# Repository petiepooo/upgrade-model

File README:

Programs: 
LED_DMA.py                 python program to run various LED patterns, including data -h gives the options
LED_DMA.c                  barebone c program that is called by LED_DMA.py to fill direct memory buffer
LED_DMA                    test shell script to run LED_DMA.py (setting all LEDs to red)
SLIDE_SHOW                 shell program to run various patterns and data displays
rpi                        directory that hosts utility program for DMA SMI access
data                       directory that holds json files with simulated data 
compile_LED_DMA            shell script to make shared library from test_LED_DMA.c
gitcommit                  program to run git from rpi to update master repository (note that you have to include an "add" for new programs )

older programs: 
test_string                shell script to run standard Python interface on GPIO18 with hardware PWA
compile_test_ctypes        shell script to make shared library from test_ctypes.c
test_ctypes.c              c program connected to test_ctypes.py
test_ctypes.py             python script to test c program access via ctypes 
test_ctypes                shell script to run test_ctypes.py with python3

The hdmi connection to the screen disturbes the precision of the hardware output to steer the LEDs. Therefore, the video needs to be turned off: 
In fact, the recommended method to run the rpi headless and start the program via tcp from a remote computer

https://www.elektronik-kompendium.de/sites/raspberry-pi/2111101.htm
/opt/vc/bin/tvservice -p; sudo /bin/chvt 6; sudo /bin/chvt 7 (gui)
/opt/vc/bin/tvservice -p; sudo /bin/chvt 2; sudo /bin/chvt 1 (console)

There also a set of software to run  o n e  LED strip using the PWR hardware clock. Here are the instruction to set up this code. You can use test_string to run a test program. 

https://tutorials-raspberrypi.de/raspberry-pi-ws2812-ws2811b-rgb-led-streifen-steuern/
provides instructions on how to install the rpi_ws281x software:

sudo apt-get update
sudo apt-get install gcc make build-essential python-dev git scons swig
sudo nano /etc/modprobe.d/snd-blacklist.conf   enter: blacklist snd_bcm2835    (in order to disable audio)
sudo nano /boot/config.txt : # Enable audio (loads snd_bcm2835)  #dtparam=audio=on (comment out)
sudo reboot
git clone https://github.com/jgarff/rpi_ws281x
cd rpi_ws281x/  : sudo scons     compile everything
sudo python3 setup.py build
sudo python3 setup.py install
sudo pip3 install adafruit-circuitpython-neopixel

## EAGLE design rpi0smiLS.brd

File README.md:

# Upgrade Model

This git repository collects programs to run a 1000+ LED model of IceCube DeepCore + Phase 1

Cloned into github from https://gitlab.rlp.net/koepke/upgrade-model

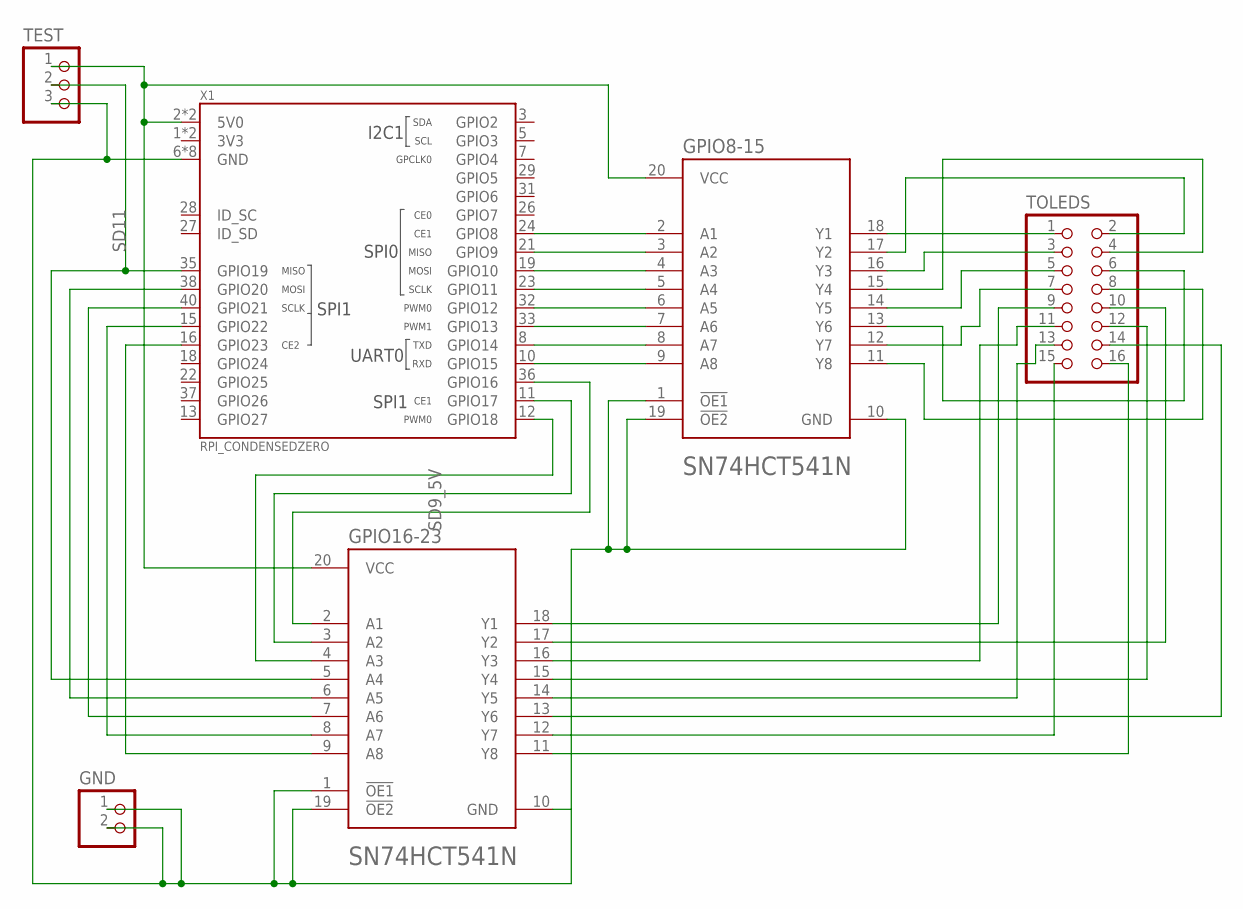
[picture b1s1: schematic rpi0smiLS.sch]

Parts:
GND: PINHD-1X2; 1X02
GPIO8-15, GPIO16-23: TEXAS_INSTRUMENTS_SN74HCT541NTEXAS_INSTRUMENTS_SN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; TEXAS_INSTRUMENTS_SN74HCT541N_0
TEST: PINHD-1X3; 1X03
TOLEDS: PINHD-2X8; 2X08
X1: RPI_CONDENSEDZERO; RPI_ZERO_THT

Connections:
3V3: X1.1 (3V3), X1.17 (3V3)
GND: GND.1, GND.2, GPIO8-15.1 (!OE1!), GPIO8-15.10 (GND), GPIO8-15.19 (!OE2!), GPIO16-23.1 (!OE1!), GPIO16-23.10 (GND), GPIO16-23.19 (!OE2!), TEST.3, X1.6 (GND), X1.9 (GND), X1.14 (GND), X1.20 (GND), X1.25 (GND), X1.30 (GND), X1.34 (GND), X1.39 (GND)
PWR: GPIO8-15.20 (VCC), GPIO16-23.20 (VCC), TEST.1, X1.2 (5V0), X1.4 (5V0)
SD0: GPIO8-15.2 (A1), X1.24 (GPIO8)
SD0_5V: GPIO8-15.18 (Y1), TOLEDS.1
SD1: GPIO8-15.3 (A2), X1.21 (GPIO9)
SD1_5V: GPIO8-15.17 (Y2), TOLEDS.2
SD2: GPIO8-15.4 (A3), X1.19 (GPIO10)
SD2_5V: GPIO8-15.16 (Y3), TOLEDS.3
SD3: GPIO8-15.5 (A4), X1.23 (GPIO11)
SD3_5V: GPIO8-15.15 (Y4), TOLEDS.4
SD4: GPIO8-15.6 (A5), X1.32 (GPIO12)
SD4_5V: GPIO8-15.14 (Y5), TOLEDS.5
SD5: GPIO8-15.7 (A6), X1.33 (GPIO13)
SD5_5V: GPIO8-15.13 (Y6), TOLEDS.6
SD6: GPIO8-15.8 (A7), X1.8 (GPIO14)
SD6_5V: GPIO8-15.12 (Y7), TOLEDS.7
SD7: GPIO8-15.9 (A8), X1.10 (GPIO15)
SD7_5V: GPIO8-15.11 (Y8), TOLEDS.8
SD8: GPIO16-23.2 (A1), X1.36 (GPIO16)
SD8_5V: GPIO16-23.18 (Y1), TOLEDS.9
SD9: GPIO16-23.3 (A2), X1.11 (GPIO17)
SD9_5V: GPIO16-23.17 (Y2), TOLEDS.10
SD10: GPIO16-23.4 (A3), X1.12 (GPIO18)
SD11: GPIO16-23.5 (A4), TEST.2, X1.35 (GPIO19)
SD11_5V: GPIO16-23.15 (Y4), TOLEDS.12
SD12: GPIO16-23.6 (A5), X1.38 (GPIO20)
SD12_5V: GPIO16-23.14 (Y5), TOLEDS.13
SD13: GPIO16-23.7 (A6), X1.40 (GPIO21)
SD13_5V: GPIO16-23.13 (Y6), TOLEDS.14
SD14: GPIO16-23.8 (A7), X1.15 (GPIO22)
SD14_5V: GPIO16-23.12 (Y7), TOLEDS.15
SD15: GPIO16-23.9 (A8), X1.16 (GPIO23)
SD15_5V: GPIO16-23.11 (Y8), TOLEDS.16
SD_10_5V: GPIO16-23.16 (Y3), TOLEDS.11

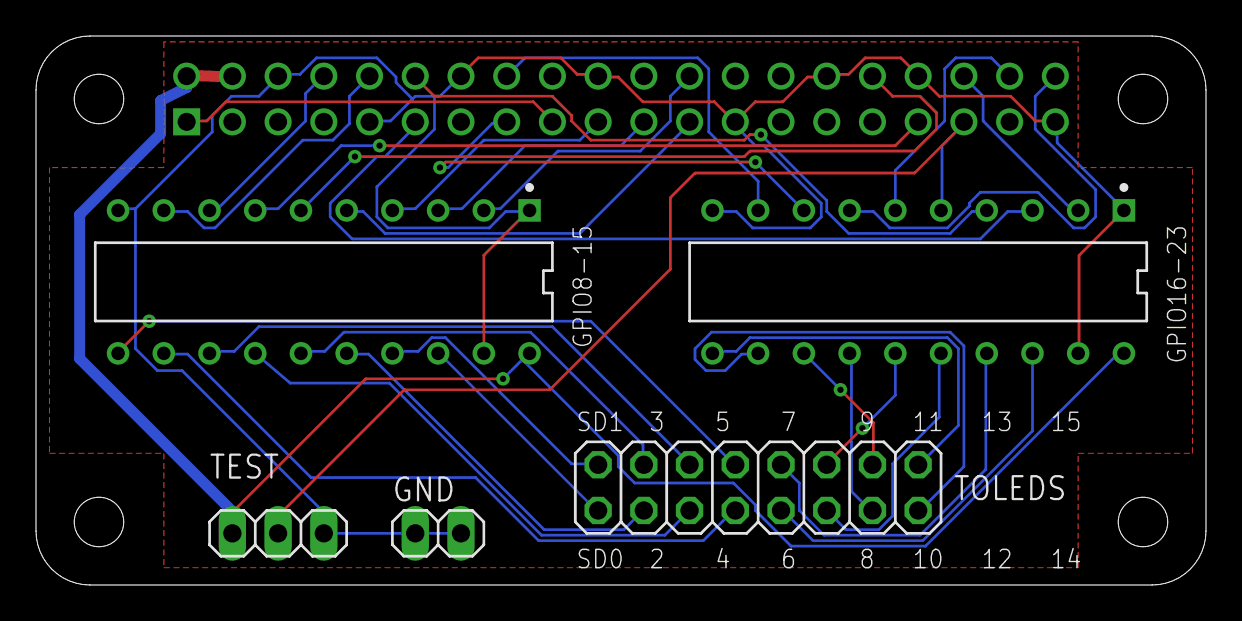
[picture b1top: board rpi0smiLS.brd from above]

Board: 2 copper layers, 65.0 x 30.5 mm, 6 parts (0 on the bottom side), 35 nets.

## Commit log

2022-01-21 eagle schematics for rpi levelshifter hat
2022-01-21 eagle board file for rpi level shifter hat
2022-02-02 update programs
2022-04-25 update readme to indicate original source location
